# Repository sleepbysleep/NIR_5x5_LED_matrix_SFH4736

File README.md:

# NIR_5x5_LED_matrix_SFH4736
5x5 LED matrix of SFH4736 and GW CSSRM1.CM ranging in Vis/Nir

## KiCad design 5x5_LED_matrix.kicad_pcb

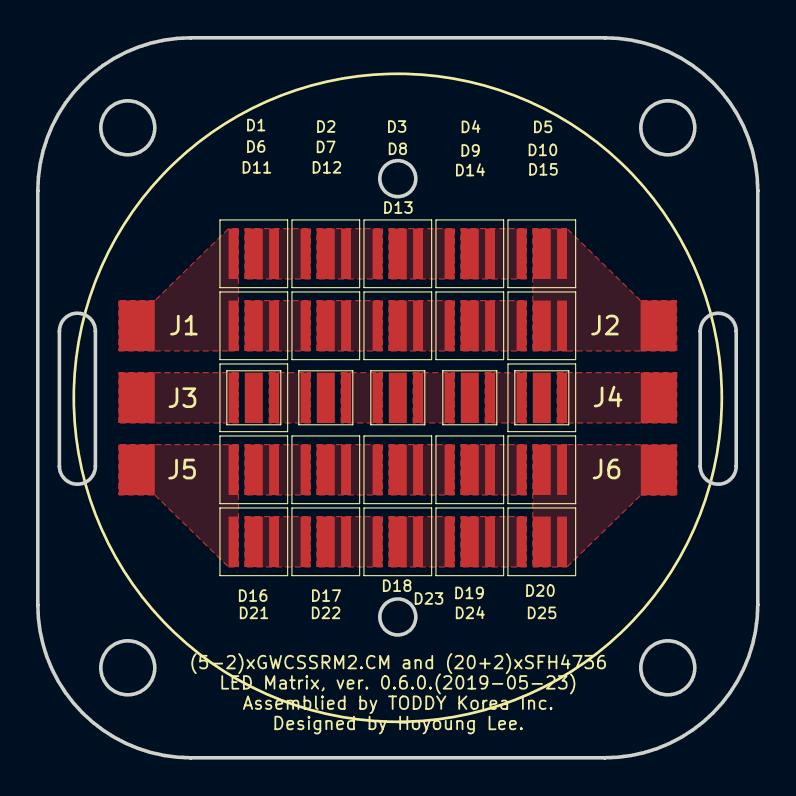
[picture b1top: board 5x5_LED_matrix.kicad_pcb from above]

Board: 2 copper layers, 40.0 x 40.0 mm, 31 parts (0 on the bottom side), 26 nets, no tracks yet.

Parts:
D1, D2, D3, D4, D5, D6, D7, D8, D9, D10, D16, D17, D18, D19, D20, D21, D22, D23, D24, D25: SFH4736; LED-SFH4736_OSRAM
D11, D12, D13, D14, D15: GW_CSSRM2.CM; LED-GWCSSRM2.CM_OSRAM
J1, J3, J5: +; SMD_1P_2.8x2.0
J2, J4, J6: -; SMD_1P_2.8x2.0

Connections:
unnamed: D1.1, D2.2
unnamed: D1.2, D6.2, J1.1
unnamed: D2.1, D3.2
unnamed: D3.1, D4.2
unnamed: D4.1, D5.2
unnamed: D6.1, D7.2
unnamed: D7.1, D8.2
unnamed: D8.1, D9.2
unnamed: D5.1, D10.1, J2.1
unnamed: D9.1, D10.2
unnamed: D11.1, D12.2
unnamed: D11.2, J3.1
unnamed: D12.1, D13.2
unnamed: D13.1, D14.2
unnamed: D14.1, D15.2
unnamed: D15.1, J4.1
unnamed: D16.1, D17.2
unnamed: D16.2, D21.2, J5.1
unnamed: D17.1, D18.2
unnamed: D18.1, D19.2
unnamed: D19.1, D20.2
unnamed: D20.1, D25.1, J6.1
unnamed: D21.1, D22.2
unnamed: D22.1, D23.2
unnamed: D23.1, D24.2
unnamed: D24.1, D25.2
